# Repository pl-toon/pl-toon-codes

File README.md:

# PL-TOON
Repository for a multi agent experimental platooning platform 

# Platform in action (Youtube Link)
PL-TOON Description and Example. Spanish audio with English subtitles (activate them in settings):
https://youtu.be/QAIMSYgBqKo

# Platoon of trains - 2024 version

# Connection Diagram (Old)

# Platform (Old)

# Acknowledgements
The development of the PL-TOON platform has been supported by the Fondecyt grant 11221365.

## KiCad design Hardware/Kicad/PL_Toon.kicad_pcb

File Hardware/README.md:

# PLTOON Hardware

The hardware for PLTOON was designed using Kicad v8.0. 
All the Kicad files can be found in [this folder](/Hardware/Kicad/)

At the core of the PCB, there is an ESP32S3 devBoard [(Schematic)](https://dl.espressif.com/dl/schematics/SCH_ESP32-S3-DevKitC-1_V1.1_20221130.pdf). It is powered using a DCDC converter module (DC-DC Buck Converter Mini 560) that takes 7.4V  (two 18350 Batteries in series) and gives a regulated 5V output voltage. The purpose of having a DCDC converter is to improve efficiency. Nevertheless, there is an option to use an LDO instead, which needs to be populated on the board. This option has not been used nor tested. 
The ESP32S3 internally regulates the 5V to generate 3.3V, which is available for the rest of the electronics.  

The 18350 batteries can be charged through the J2 connector by switching SW1 to the Off/Chg state. There is no protection for reverse polarity, so it is up to the user to connect it correctly. When no charger is connected, the PLTOON remains OFF with this SW1 position. 
The power from the battery is supplied to the rest of the circuit by moving the switch SW1 to ON, which turns the LED1 ON (if the batteries are connected correctly) and LED2 ON (if the 5V of the DCDC converter is being supplied). Resistors R1 and R6 were chosen to be 330 Ohm, but they can be increased in value if we want to dim the LED light. 

A TB6612FNG H-Bridge is connected to the ESP32S3, and two motors can be driven by connecting them to J8 and J9 connectors. 

A distance sensor like VL53L0X can be connected to J1 using I2C. Other GPIOs are available in case they are needed. Pull-up resistors R2-R5 are not populated in the board, but are available for use. 

A Velocity sensor can be connected to USB-OTG by connecting it directly to the right-hand side USB-c connector of the ESP32S3 devBoard or to connector J7. J7 can also be used to flash the ESP32S3 devBoard using USB-OTG.
An SPI velocity sensor can be connected to connectors J5, J4 and J6 (depending on the signals that are needed). 

A top view of the rendered 3d PCB design in Kicad is shown below. 

A bottom view of the rendered 3d PCB design in Kicad is shown below. 

# Finished PCB
Some pictures of the assembled PCBs are shown below. 

Charging the batteries

Using the H-bridge with a DC motor connected

USB-OTG connected 

# Schematic in pdf
[Schematic in pdf](/Hardware/Kicad/PL_Toon.pdf)

# BOM 
The bill of Material can be found [here](/Hardware/Kicad/BOM_PLTOON)

# Production Files (Gerber)
The .zip file used for producing the PCBs can be found [here](/Hardware/Production_Files)

# 3d Step file
[3d Step File](/Hardware/Kicad/PL_Toon_3D.step)

# 3d Printed Parts
The 3MF models for the printed train parts can be found [here](/Hardware/3D_Printed_Parts).

The chassis is made of two parts, a front one and a rear one. Each of them comes in two versions: the file ending in `_IMPRIMIR` holds a single copy of the part, and the one ending in `_DUPLICADAx8` is a plate with 8 copies already arranged for printing a full batch.

| File | Description |
| --- | --- |
| [PIEZA_FRONTAL_TREN_IMPRIMIR.3mf](/Hardware/3D_Printed_Parts/PIEZA_FRONTAL_TREN_IMPRIMIR.3mf) | Front chassis part, single copy |
| [PIEZA_FRONTAL_TREN_DUPLICADAx8.3mf](/Hardware/3D_Printed_Parts/PIEZA_FRONTAL_TREN_DUPLICADAx8.3mf) | Front chassis part, plate with 8 copies |
| [PIEZA_POSTERIOR_TREN_IMPRIMIR.3mf](/Hardware/3D_Printed_Parts/PIEZA_POSTERIOR_TREN_IMPRIMIR.3mf) | Rear chassis part, single copy |
| [PIEZA_POSTERIOR_TREN_DUPLICADAx8.3mf](/Hardware/3D_Printed_Parts/PIEZA_POSTERIOR_TREN_DUPLICADAx8.3mf) | Rear chassis part, plate with 8 copies |
| [Arandela_trencito.3mf](/Hardware/3D_Printed_Parts/Arandela_trencito.3mf) | Washer, single copy |

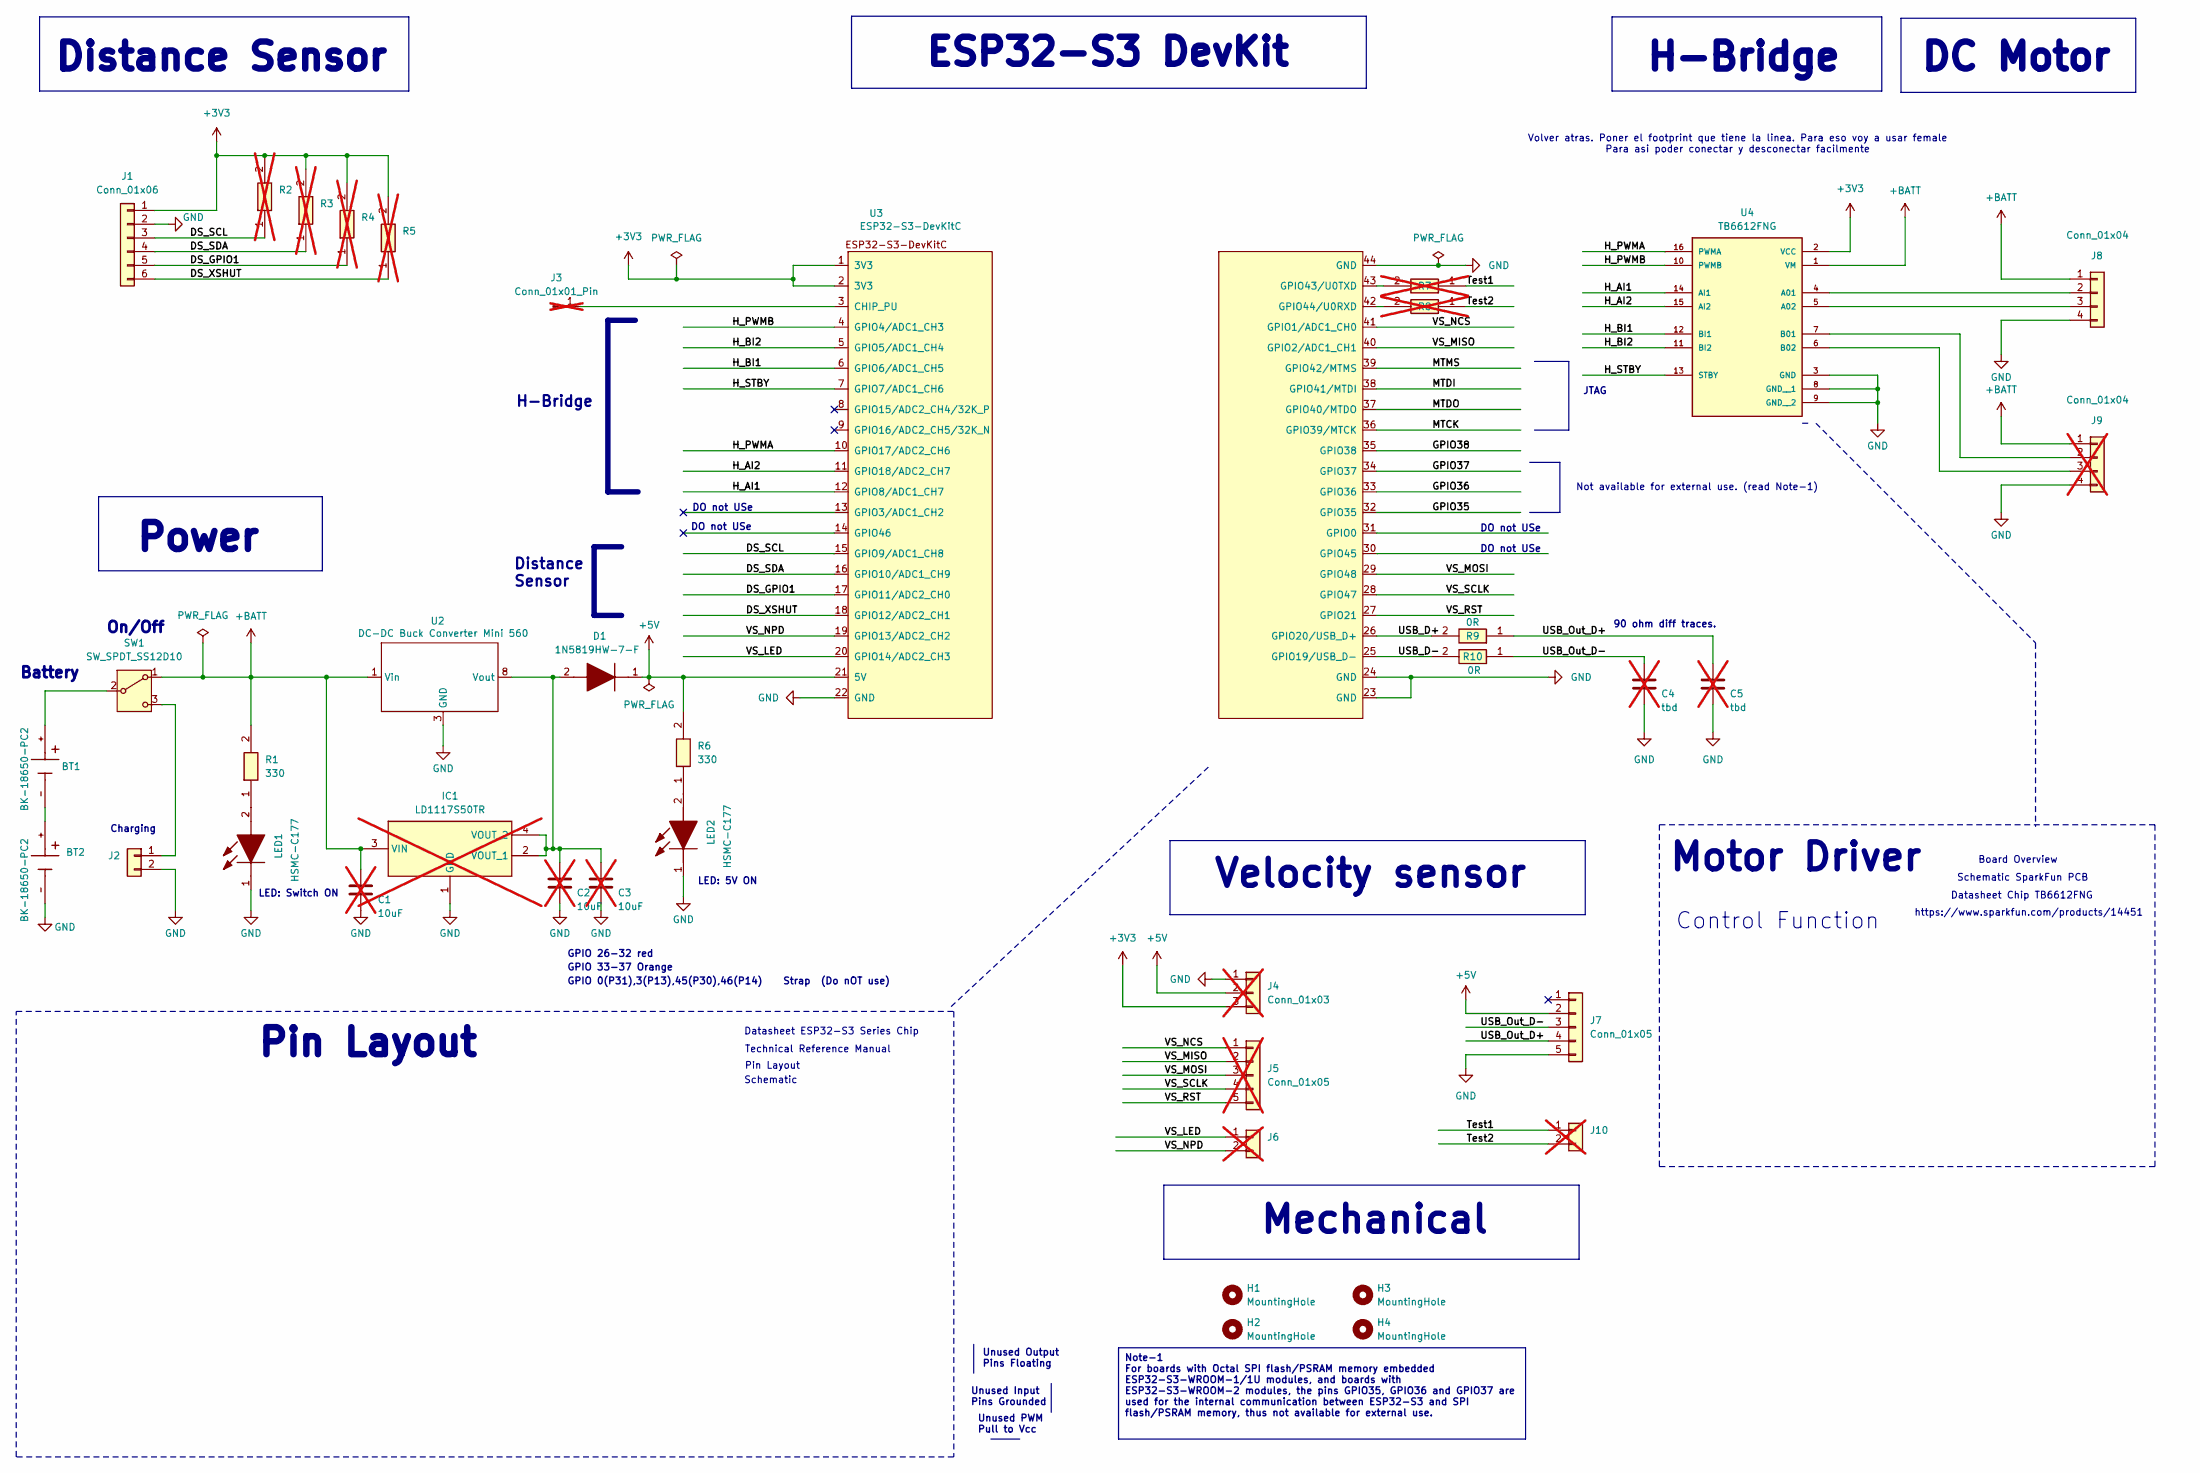
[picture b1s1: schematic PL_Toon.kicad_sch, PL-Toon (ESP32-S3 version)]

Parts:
BT1, BT2: BK-18650-PC2; BAT_BK-18650-PC2; PARTREV F
C1, C2, C3: 10uF; C_1206_3216Metric; not fitted
C4, C5: tbd; C_1206_3216Metric; not fitted
D1: 1N5819HW-7-F; D_SOD-123; Mouser Part Number 621-1N5819HW-F
H1, H2, H3, H4: MountingHole; MountingHole_3.2mm_M3
IC1: LD1117S50TR; SOT230P700X190-4N; Mouser Part Number 511-LD1117S50; not fitted
J1: Conn_01x06; JST_PH_B6B-PH-K_1x06_P2.00mm_Vertical
J2: Conn_01x02; JST_PH_B2B-PH-K_1x02_P2.00mm_Vertical
J3: Conn_01x01_Pin; PinHeader_1x01_P2.54mm_Vertical; not fitted
J4: Conn_01x03; JST_PH_B3B-PH-K_1x03_P2.00mm_Vertical; not fitted
J5: Conn_01x05; JST_PH_B5B-PH-K_1x05_P2.00mm_Vertical; not fitted
J6, J10: Conn_01x02; JST_PH_B2B-PH-K_1x02_P2.00mm_Vertical; not fitted
J7: Conn_01x05; JST_PH_B5B-PH-K_1x05_P2.00mm_Vertical
J8: Conn_01x04; JST_PH_B4B-PH-K_1x04_P2.00mm_Vertical
J9: Conn_01x04; JST_PH_B4B-PH-K_1x04_P2.00mm_Vertical; not fitted
LED1, LED2: HSMC-C177; LED_1206_3216Metric_Pad1.42x1.75mm_HandSolder; Mouser Part Number 630-HSMC-C177
R1, R6: 330; R_1206_3216Metric_Pad1.30x1.75mm_HandSolder
R2, R3, R4, R5, R7, R8: R_1206_3216Metric_Pad1.30x1.75mm_HandSolder; not fitted
R9, R10: 0R; R_1206_3216Metric_Pad1.30x1.75mm_HandSolder
SW1: SW_SPDT_SS12D10; SS12D10
U2: DC-DC Buck Converter Mini 560; Mini560
U3: ESP32-S3-DevKitC
U4: TB6612FNG; MODULE_ROB-14450; PARTREV 11-13-17

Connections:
+3V3: J1.1, J4.3, R2.2, R3.2, R4.2, R5.2, U3.1 (3V3), U3.2 (3V3), U4.2 (VCC)
+5V: D1.1 (K), J4.2, J7.2, R6.2, U3.21 (5V)
+BATT: C1.1, IC1.3 (VIN), J8.1, J9.1, R1.2, SW1.1 (A), U2.1 (Vin), U2.2 (Vin), U4.1 (VM)
/DS_GPIO1: J1.5, R4.1, U3.17 (GPIO11/ADC2_CH0)
/DS_SCL: J1.3, R2.1, U3.15 (GPIO9/ADC1_CH8)
/DS_SDA: J1.4, R3.1, U3.16 (GPIO10/ADC1_CH9)
/DS_XSHUT: J1.6, R5.1, U3.18 (GPIO12/ADC2_CH1)
/GPIO35: U3.32 (GPIO35)
/GPIO36: U3.33 (GPIO36)
/GPIO37: U3.34 (GPIO37)
/GPIO38: U3.35 (GPIO38)
/H_AI1: U3.12 (GPIO8/ADC1_CH7), U4.14 (AI1)
/H_AI2: U3.11 (GPIO18/ADC2_CH7), U4.15 (AI2)
/H_BI1: U3.6 (GPIO6/ADC1_CH5), U4.12 (BI1)
/H_BI2: U3.5 (GPIO5/ADC1_CH4), U4.11 (BI2)
/H_PWMA: U3.10 (GPIO17/ADC2_CH6), U4.16 (PWMA)
/H_PWMB: U3.4 (GPIO4/ADC1_CH3), U4.10 (PWMB)
/H_STBY: U3.7 (GPIO7/ADC1_CH6), U4.13 (STBY)
/MTCK: U3.36 (GPIO39/MTCK)
/MTDI: U3.38 (GPIO41/MTDI)
/MTDO: U3.37 (GPIO40/MTDO)
/MTMS: U3.39 (GPIO42/MTMS)
/Test1: J10.1, R7.1
/Test2: J10.2, R8.1
/USB_D+: R9.2, U3.26 (GPIO20/USB_D+)
/USB_D-: R10.2, U3.25 (GPIO19/USB_D-)
/USB_Out_D+: C5.1, J7.4, R9.1
/USB_Out_D-: C4.1, J7.3, R10.1
/VS_LED: J6.1, U3.20 (GPIO14/ADC2_CH3)
/VS_MISO: J5.2, U3.40 (GPIO2/ADC1_CH1)
/VS_MOSI: J5.3, U3.29 (GPIO48)
/VS_NCS: J5.1, U3.41 (GPIO1/ADC1_CH0)
/VS_NPD: J6.2, U3.19 (GPIO13/ADC2_CH2)
/VS_RST: J5.5, U3.27 (GPIO21)
/VS_SCLK: J5.4, U3.28 (GPIO47)
GND: BT2.-, C1.2, C2.2, C3.2, C4.2, C5.2, IC1.1 (GND), J1.2, J2.2, J4.1, J7.5, J8.4, J9.4, LED1.1 (K), LED2.1 (K), U2.3 (GND), U2.4 (GND), U2.5 (GND), U2.6 (GND), U3.22 (GND), U3.23 (GND), U3.24 (GND), U3.44 (GND), U4.3 (GND), U4.8 (GND__1), U4.9 (GND__2)
unnamed: BT1.-, BT2.+
unnamed: C2.1, C3.1, D1.2 (A), IC1.2 (VOUT_1), IC1.4 (VOUT_2), U2.7 (Vout), U2.8 (Vout)
unnamed: J2.1, SW1.3 (C)
unnamed: J3.1, U3.3 (CHIP_PU)
unnamed: J8.2, U4.4 (A01)
unnamed: J8.3, U4.5 (A02)
unnamed: J9.2, U4.7 (B01)
unnamed: J9.3, U4.6 (B02)
unnamed: LED1.2 (A), R1.1
unnamed: LED2.2 (A), R6.1
unnamed: BT1.+, SW1.2 (B)
unnamed: R7.2, U3.43 (GPIO43/U0TXD)
unnamed: R8.2, U3.42 (GPIO44/U0RXD)

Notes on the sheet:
Note-1 For boards with Octal SPI flash/PSRAM memory embedded ESP32-S3-WROOM-1/1U modules, and boards with ESP32-S3-WROOM-2 modules, the pins GPIO35, GPIO36 and GPIO37 are used for the internal communication between ESP32-S3 and SPI flash/PSRAM memory, thus not available for external use.
Pin Layout
Velocity sensor
Mechanical
https://www.sparkfun.com/products/14451
Unused PWM Pull to Vcc
LED: 5V ON
GPIO 0(P31),3(P13),45(P30),46(P14) Strap (Do nOT use)
Battery
Distance Sensor
Unused Input Pins Grounded
90 ohm diff traces.
H-Bridge
Pin Layout
Motor Driver
GPIO 26-32 red
Technical Reference Manual
ESP32-S3 DevKit
Schematic
GPIO 33-37 Orange
DO not USe
Unused Output Pins Floating
Control Function
Charging
Schematic SparkFun PCB
Not available for external use. (read Note-1)
Datasheet Chip TB6612FNG
H-Bridge
Distance Sensor
Board Overview
DC Motor
Datasheet ESP32-S3 Series Chip
Power
LED: Switch ON
On/Off
Volver atras. Poner el footprint que tiene la linea. Para eso voy a usar female Para asi poder conectar y desconectar facilmente
JTAG

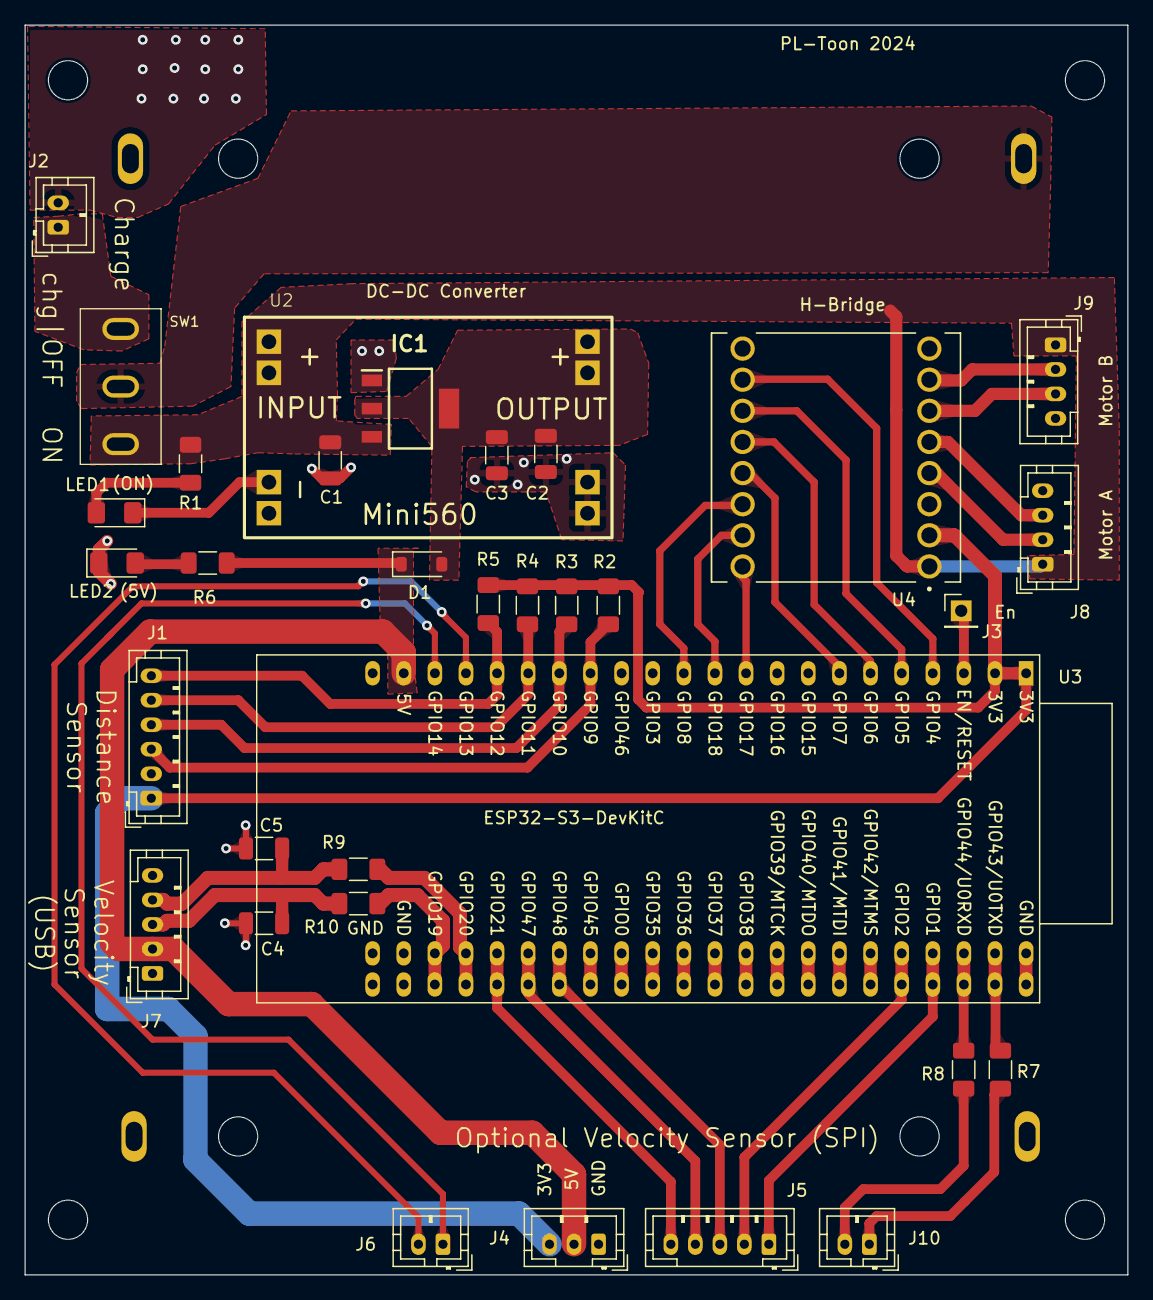
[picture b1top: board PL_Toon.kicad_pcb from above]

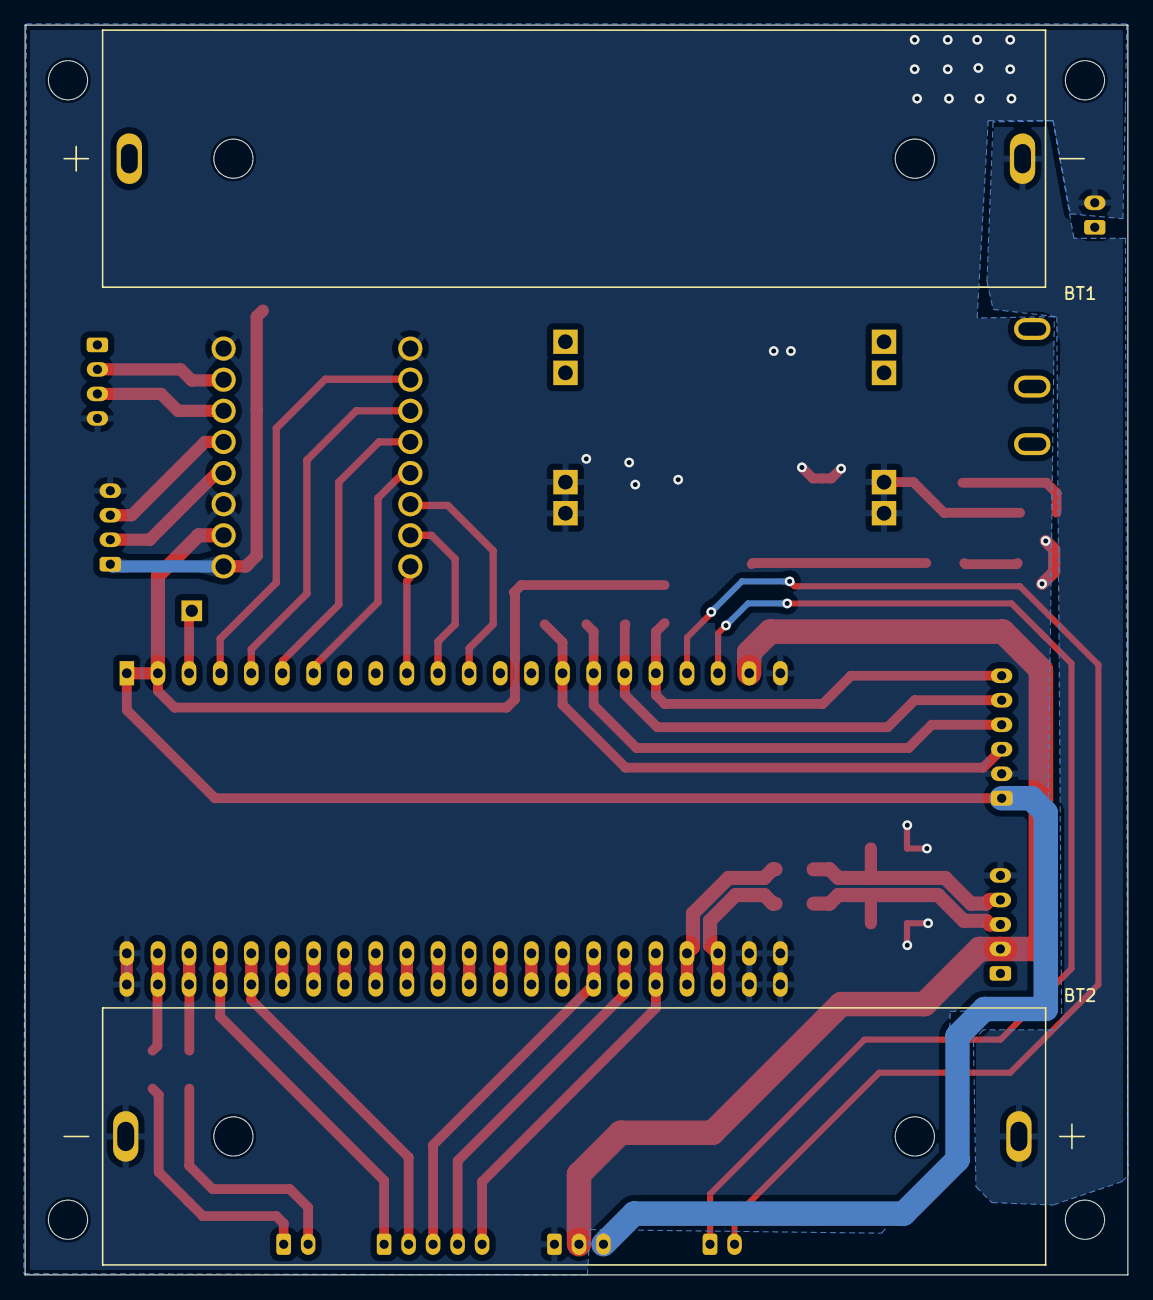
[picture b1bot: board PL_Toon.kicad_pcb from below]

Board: 2 copper layers, 90.0 x 102.0 mm, 39 parts (2 on the bottom side), 41 nets.

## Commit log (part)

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2021-01-10 uploaded code to capture espnow data from the agents
2021-01-10 uploaded code for the agents
2021-01-10 readme esp32 code
2021-01-11 uploaded fusion360 images
2021-02-04 Create stl
2021-02-04 deleted extra files
2021-02-05 Se agrega Link de Video en README
2021-03-10 Basic dashboard (work-in-progress)
2021-03-22 code cleaning
2021-03-23 clean leader code
2021-03-23 clean PID agents code
2021-03-27 uploaded code to calibrate the camera lens
2021-03-27 name change to *.ino files and small typos fixed
2021-03-29 fixed tabs
2021-03-29 added time headway MQTT topic
2021-03-31 lens calibration readme
2021-04-29 cambio error variable
2021-09-28 update 09/2021
2021-09-28 edit CaptureData
2021-09-29 added led to indicate when the setup is done
2021-11-30 Codigo Diego tracking velocidad
2021-12-02 codigo correccion de datos Cristóbal
2021-12-02 Código para control crucero con comunicación entre carro
2022-01-03 pruebas camara 01/2022
2022-01-03 Rename README.txt to README.md
2022-03-03 ejemplo envio espnow
2022-04-14 update plot RT now using UDP
2022-04-18 inclusion udp a codigo tren
2022-04-21 revision codigo control posicion con comunicacion
2022-04-28 fix eje temporal matplot_realtime
2022-05-04 codigo FUNCIONAL mayo 4 2022
2022-05-04 mod plot
2022-05-17 prueba 17 mayo
2022-05-26 codigo 17 mayo
2022-05-26 code experiments delay
2022-05-27 pruebas delay 27-05
2022-05-27 codigo delay 27-05
2024-01-26 Lista Tren
2024-08-05 Create Production_PCB_100624.zip
    Zip File sent to production
2024-10-04 Kicad PCB 1st version
2025-02-14 Update the PCB files
    - Updated the files, to take into account small changes like Do Not Populate, and add resistors values to 330 Ohm in the case of the LED resistors.
    - Added Bill Of Material
2025-02-14 Create Pictures folder
2025-02-14 Some Pictures of the PCBs
2025-02-14 Update README.md
    Working in progress, writing description of the PCB
2025-02-14 Simple test code for hardware
    - test motor
    -Test dist sensor
2025-11-28 update to new version
    new image of a platoon of trains v2.0
2025-11-28 Update README.md for 2024 version
    new image
2025-11-28 Format README.md for improved clarity
    added Old to images of the previous version
